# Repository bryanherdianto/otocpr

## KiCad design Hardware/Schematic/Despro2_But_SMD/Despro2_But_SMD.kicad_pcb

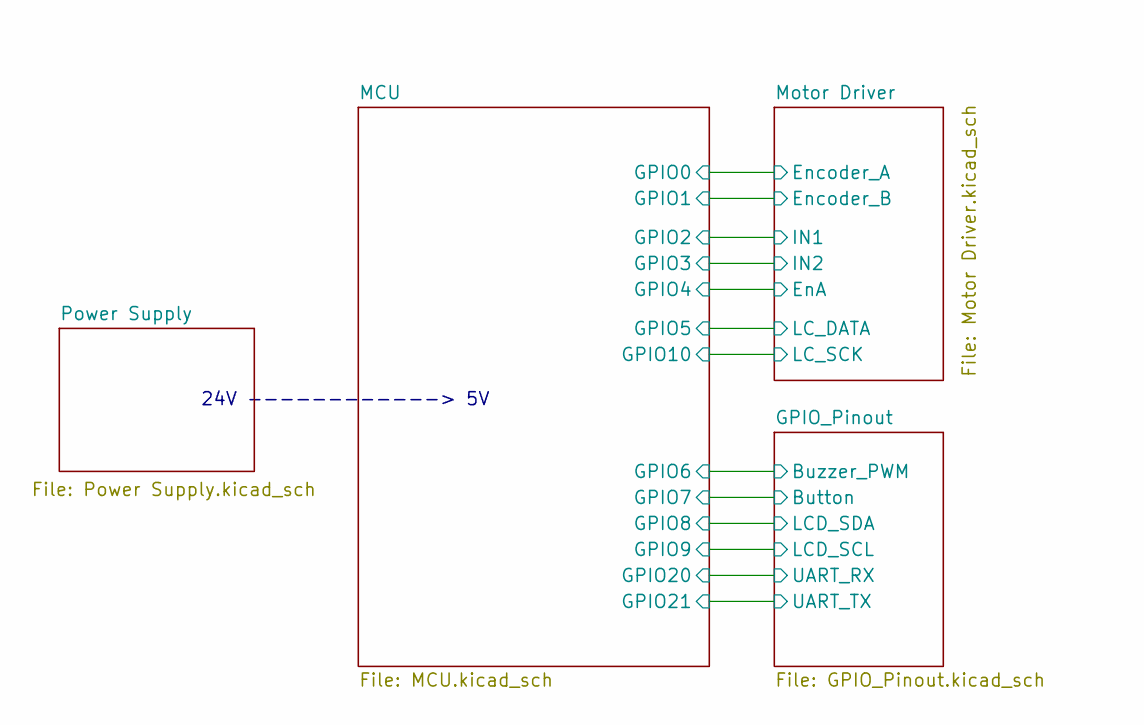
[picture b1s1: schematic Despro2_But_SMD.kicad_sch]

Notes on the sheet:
24V ------------> 5V

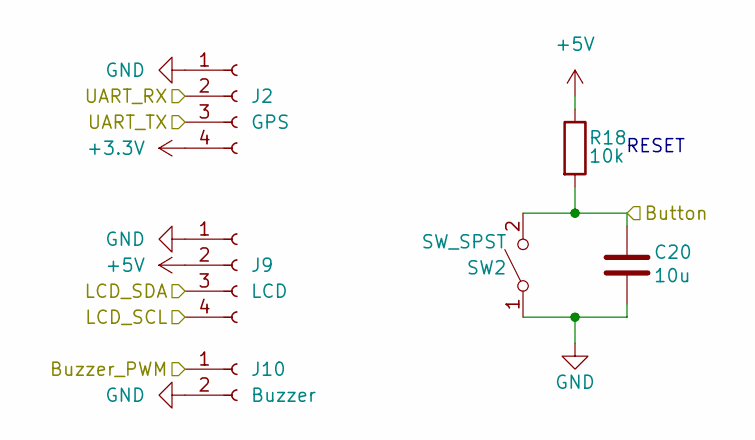
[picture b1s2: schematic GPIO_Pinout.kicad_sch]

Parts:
C20: 10u; C_1206_3216Metric_Pad1.33x1.80mm_HandSolder; MANUFACTURER_PART_NUMBER GRM188D71A106KA73D
J2: GPS; Molex_SL_171971-0004_1x04_P2.54mm_Vertical
J9: LCD; Molex_SL_171971-0004_1x04_P2.54mm_Vertical
J10: Buzzer; Molex_SL_171971-0002_1x02_P2.54mm_Vertical
R18: 10k; R_1206_3216Metric_Pad1.30x1.75mm_HandSolder; MANUFACTURER_PART_NUMBER RT0603FRE0710KL
SW2: SW_SPST; SW_PUSH_6mm; MANUFACTURER_PART_NUMBER TL1105F160QWITHSTRAIGHT

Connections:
+3.3V: J2.4; also elsewhere on the board
+5V: J9.2, R18.1; also elsewhere on the board
/MCU/GPIO6: J10.1; also elsewhere on the board
/MCU/GPIO7: C20.1, R18.2, SW2.2 (B); also elsewhere on the board
/MCU/GPIO8: J9.3; also elsewhere on the board
/MCU/GPIO9: J9.4; also elsewhere on the board
/MCU/GPIO20: J2.2; also elsewhere on the board
/MCU/GPIO21: J2.3; also elsewhere on the board
GND: C20.2, J2.1, J9.1, J10.2, SW2.1 (A); also elsewhere on the board

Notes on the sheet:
RESET

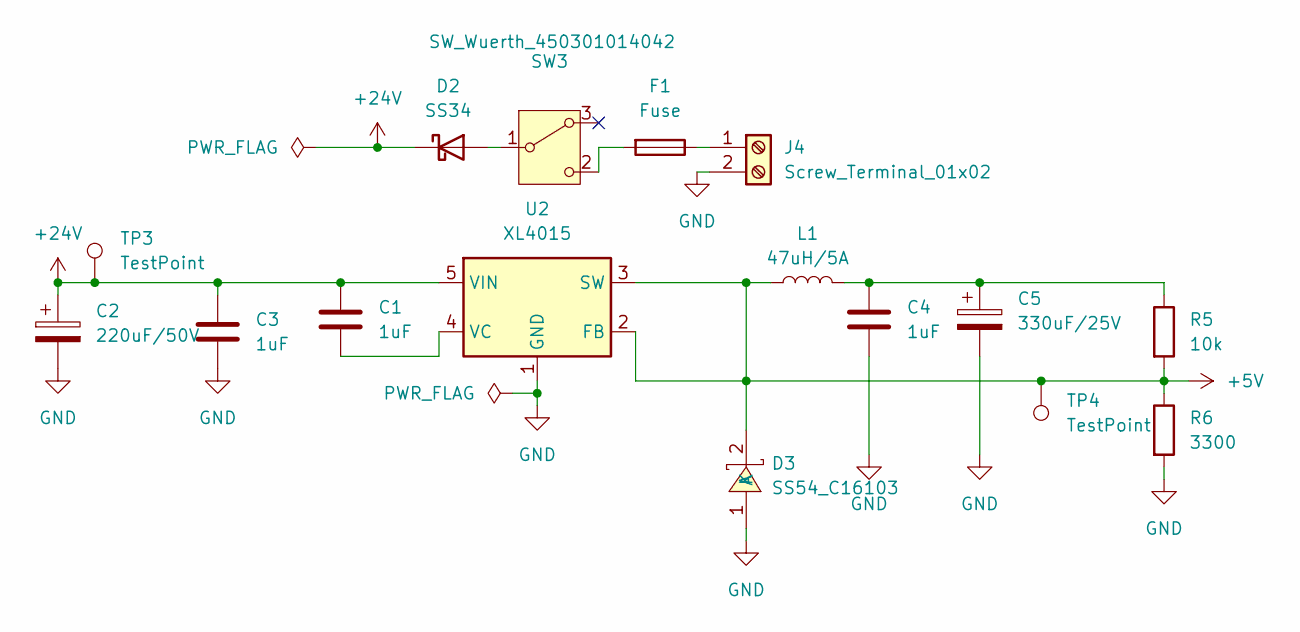
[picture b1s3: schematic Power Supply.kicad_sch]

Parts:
C1, C3, C4: 1uF; C_1206_3216Metric_Pad1.33x1.80mm_HandSolder
C2: 220uF/50V; CP_Radial_D10.0mm_P5.00mm
C5: 330uF/25V; CP_Radial_D10.0mm_P5.00mm
D2: SS34; D_SMA
D3: SS54_C16103; SMC_L7.1-W6.2-LS8.1-R-RD; MPN SS54C; LCSC Part C16103
F1: Fuse; Fuse_1206_3216Metric_Pad1.42x1.75mm_HandSolder
J4: Screw_Terminal_01x02; TerminalBlock_Phoenix_PT-1,5-2-3.5-H_1x02_P3.50mm_Horizontal
L1: 47uH/5A; L_Sunlord_MWSA1206S-1R5
R5: 10k; R_1206_3216Metric_Pad1.30x1.75mm_HandSolder
R6: 3300; R_1206_3216Metric_Pad1.30x1.75mm_HandSolder
SW3: SW_Wuerth_450301014042; SW_Slide-03_Wuerth-WS-SLTV_10x2.5x6.4_P2.54mm
TP3, TP4: TestPoint; PinHeader_1x01_P2.54mm_Vertical
U2: XL4015; TO-263-5_TabPin3

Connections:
+5V: D3.2 (K), L1.1, R5.2, R6.1, TP4.1 (1_1), U2.2 (FB), U2.3 (SW); also elsewhere on the board
+24V: C1.1, C2.1, C3.1, D2.1 (K), TP3.1 (1_1), U2.5 (VIN); also elsewhere on the board
GND: C2.2, C3.2, C4.2, C5.2, D3.1 (A), J4.2, R6.2, U2.1 (GND); also elsewhere on the board
unnamed: C4.1, C5.1, L1.2, R5.1
unnamed: D2.2 (A), SW3.1 (B)
unnamed: F1.1, J4.1
unnamed: F1.2, SW3.2 (C)
unnamed: C1.2, U2.4 (VC)

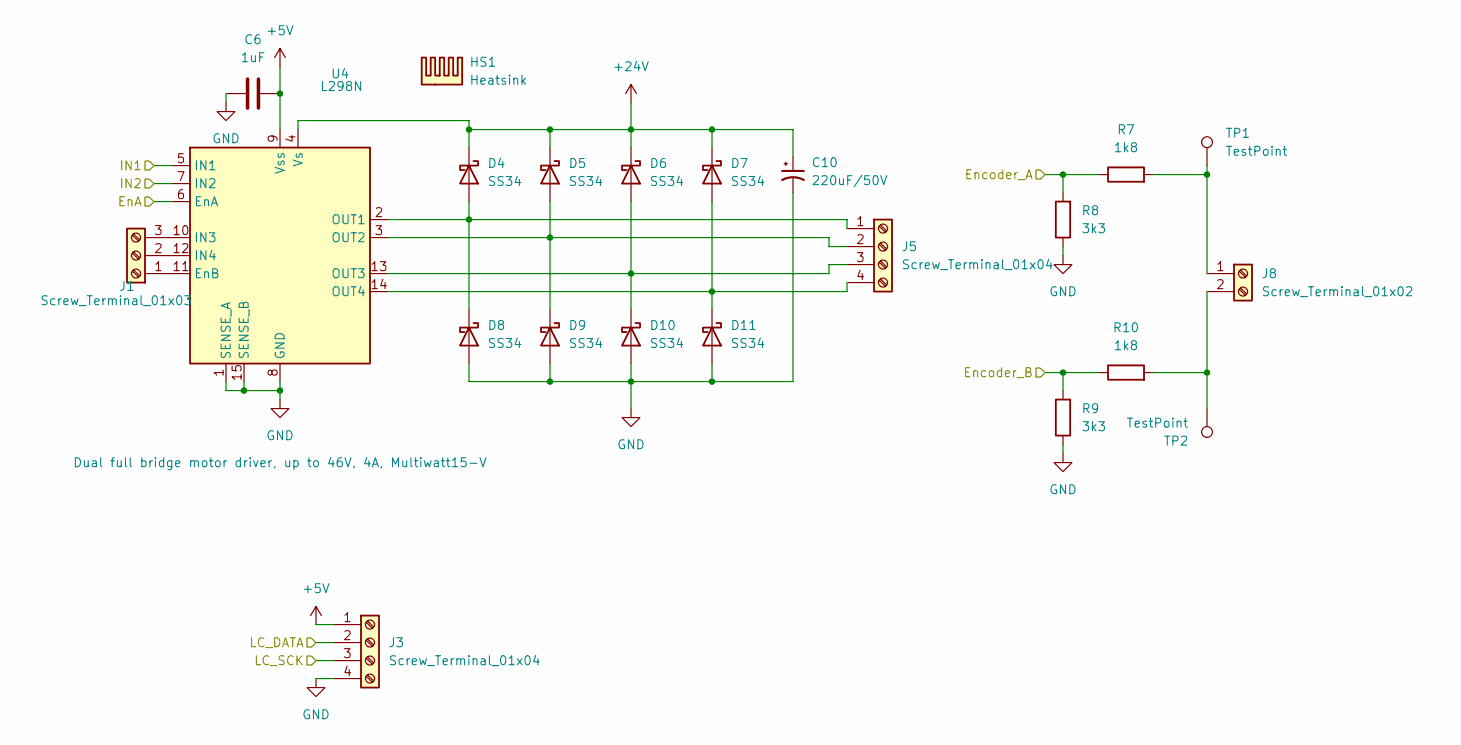
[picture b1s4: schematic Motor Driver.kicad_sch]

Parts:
C6: 1uF; C_1206_3216Metric_Pad1.33x1.80mm_HandSolder
C10: 220uF/50V; CP_Radial_D10.0mm_P5.00mm
D4, D5, D6, D7, D8, D9, D10, D11: SS34; D_SMA
HS1: Heatsink
J1: Screw_Terminal_01x03; TerminalBlock_Phoenix_PT-1,5-3-3.5-H_1x03_P3.50mm_Horizontal
J3, J5: Screw_Terminal_01x04; TerminalBlock_Phoenix_PT-1,5-4-3.5-H_1x04_P3.50mm_Horizontal
J8: Screw_Terminal_01x02; TerminalBlock_Phoenix_PT-1,5-2-3.5-H_1x02_P3.50mm_Horizontal
R7, R10: 1k8; R_1206_3216Metric_Pad1.30x1.75mm_HandSolder
R8, R9: 3k3; R_1206_3216Metric_Pad1.30x1.75mm_HandSolder
TP1, TP2: TestPoint; PinHeader_1x01_P2.54mm_Vertical
U4: L298N; TO-220-15_P2.54x5.08mm_StaggerOdd_Lead4.58mm_Vertical

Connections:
+5V: C6.2, J3.1, U4.9 (Vss); also elsewhere on the board
+24V: C10.1, D4.1 (K), D5.1 (K), D6.1 (K), D7.1 (K), U4.4 (Vs); also elsewhere on the board
/MCU/GPIO0: R7.1, R8.2; also elsewhere on the board
/MCU/GPIO1: R9.2, R10.1; also elsewhere on the board
/MCU/GPIO2: U4.5 (IN1); also elsewhere on the board
/MCU/GPIO3: U4.7 (IN2); also elsewhere on the board
/MCU/GPIO4: U4.6 (EnA); also elsewhere on the board
/MCU/GPIO5: J3.2; also elsewhere on the board
/MCU/GPIO10: J3.3; also elsewhere on the board
GND: C6.1, C10.2, D8.2 (A), D9.2 (A), D10.2 (A), D11.2 (A), J3.4, R8.1, R9.1, U4.1 (SENSE_A), U4.8 (GND), U4.15 (SENSE_B); also elsewhere on the board
unnamed: D4.2 (A), D8.1 (K), J5.1, U4.2 (OUT1)
unnamed: D5.2 (A), D9.1 (K), J5.2, U4.3 (OUT2)
unnamed: D6.2 (A), D10.1 (K), J5.3, U4.13 (OUT3)
unnamed: D7.2 (A), D11.1 (K), J5.4, U4.14 (OUT4)
unnamed: J1.1, U4.11 (EnB)
unnamed: J1.2, U4.12 (IN4)
unnamed: J1.3, U4.10 (IN3)
unnamed: J8.1, R7.2, TP1.1 (1_1)
unnamed: J8.2, R10.2, TP2.1 (1_1)

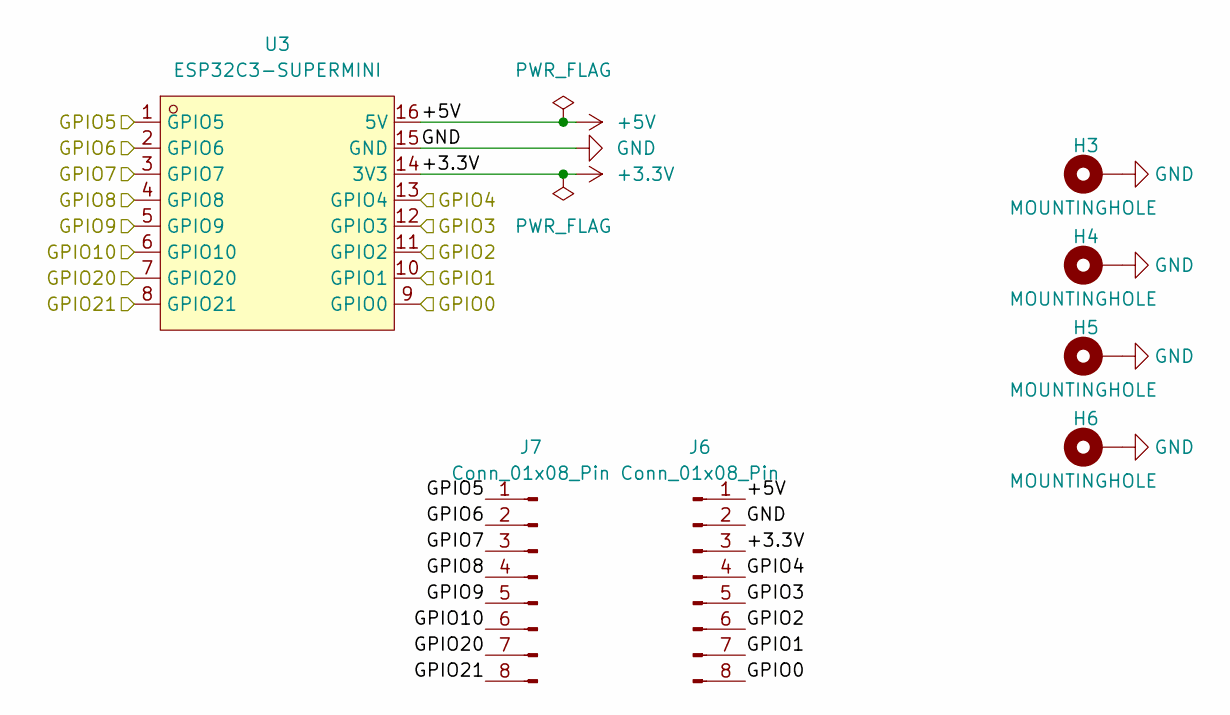
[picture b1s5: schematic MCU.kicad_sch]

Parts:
H3, H4, H5, H6: MOUNTINGHOLE; MountingHole_3.2mm_M3_Pad_Via
J6, J7: Conn_01x08_Pin; PinSocket_1x08_P2.54mm_Vertical
U3: ESP32C3-SUPERMINI; ESP32-C3-SuperMini_THT.; MPN ESP32C3-SuperMini; LCSC Part C9900147397

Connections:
+3.3V: J6.3, U3.14 (3V3); also elsewhere on the board
+5V: J6.1, U3.16 (5V); also elsewhere on the board
/MCU/GPIO0: J6.8, U3.9 (GPIO0); also elsewhere on the board
/MCU/GPIO1: J6.7, U3.10 (GPIO1); also elsewhere on the board
/MCU/GPIO2: J6.6, U3.11 (GPIO2); also elsewhere on the board
/MCU/GPIO3: J6.5, U3.12 (GPIO3); also elsewhere on the board
/MCU/GPIO4: J6.4, U3.13 (GPIO4); also elsewhere on the board
/MCU/GPIO5: J7.1, U3.1 (GPIO5); also elsewhere on the board
/MCU/GPIO6: J7.2, U3.2 (GPIO6); also elsewhere on the board
/MCU/GPIO7: J7.3, U3.3 (GPIO7); also elsewhere on the board
/MCU/GPIO8: J7.4, U3.4 (GPIO8); also elsewhere on the board
/MCU/GPIO9: J7.5, U3.5 (GPIO9); also elsewhere on the board
/MCU/GPIO10: J7.6, U3.6 (GPIO10); also elsewhere on the board
/MCU/GPIO20: J7.7, U3.7 (GPIO20); also elsewhere on the board
/MCU/GPIO21: J7.8, U3.8 (GPIO21); also elsewhere on the board
GND: H3.1 (1_1), H4.1 (1_1), H5.1 (1_1), H6.1 (1_1), J6.2, U3.15 (GND); also elsewhere on the board

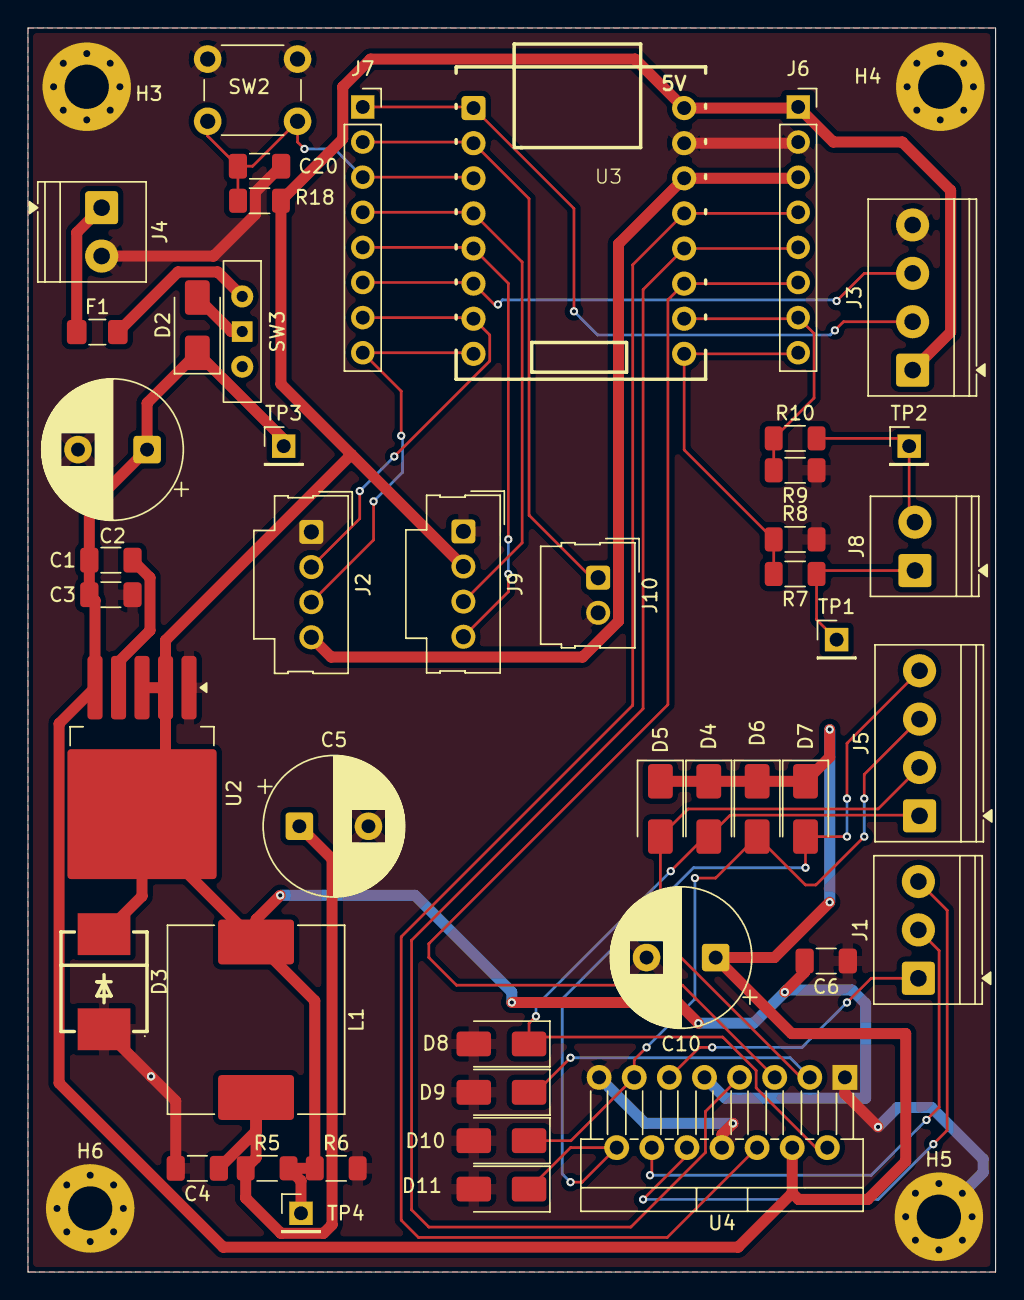
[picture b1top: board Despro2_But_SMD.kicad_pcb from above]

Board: 2 copper layers, 70.0 x 90.0 mm, 50 parts (0 on the bottom side), 31 nets.
